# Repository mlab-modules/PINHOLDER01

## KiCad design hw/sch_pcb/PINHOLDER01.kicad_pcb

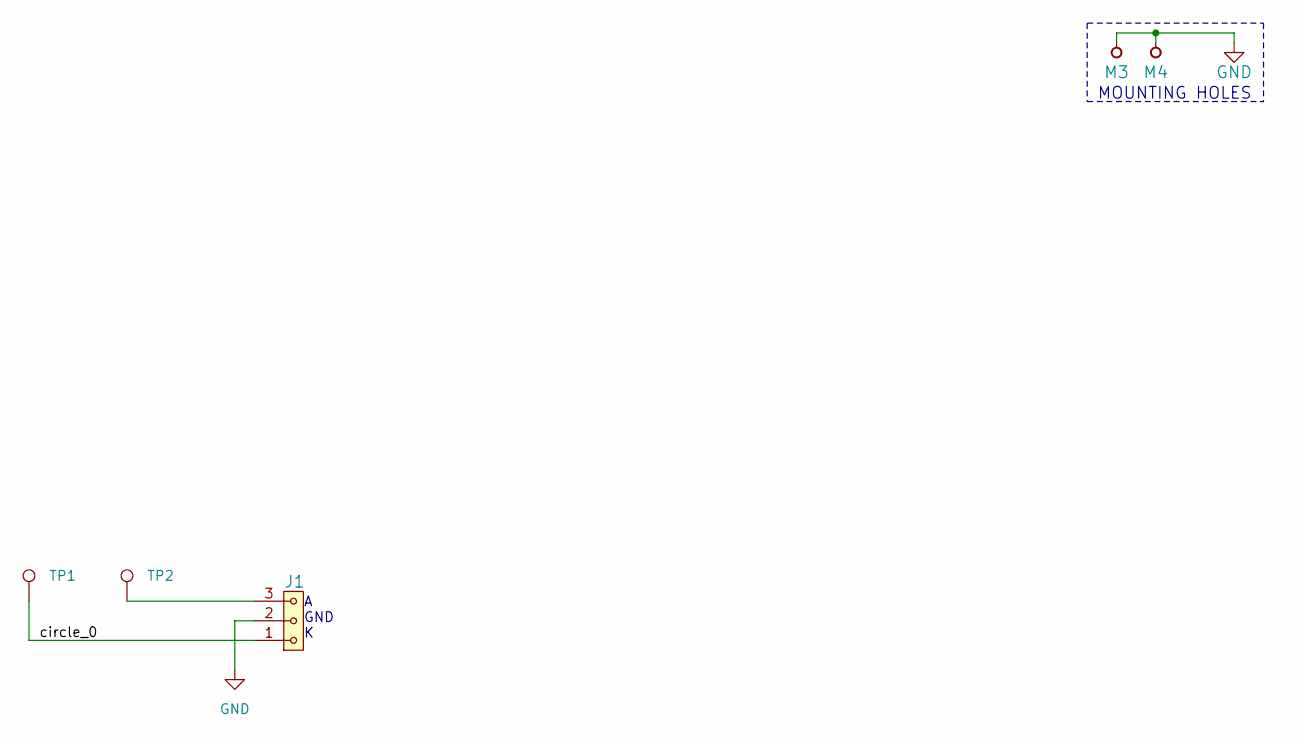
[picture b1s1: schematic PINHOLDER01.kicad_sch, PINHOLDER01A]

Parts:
J1: HEADER_1x03; PinHeader_1x03_P2.54mm_Vertical_SMD_Pin1Left
M3, M4: HOLE; MountingHole_3mm
TP1, TP2: TestPoint; TestPoint_Pad_D0.5mm_noSilk

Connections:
/circle_0: J1.1, TP1.1
GND: J1.2, M3.1, M4.1
unnamed: J1.3, TP2.1

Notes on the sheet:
MOUNTING HOLES
A GND K

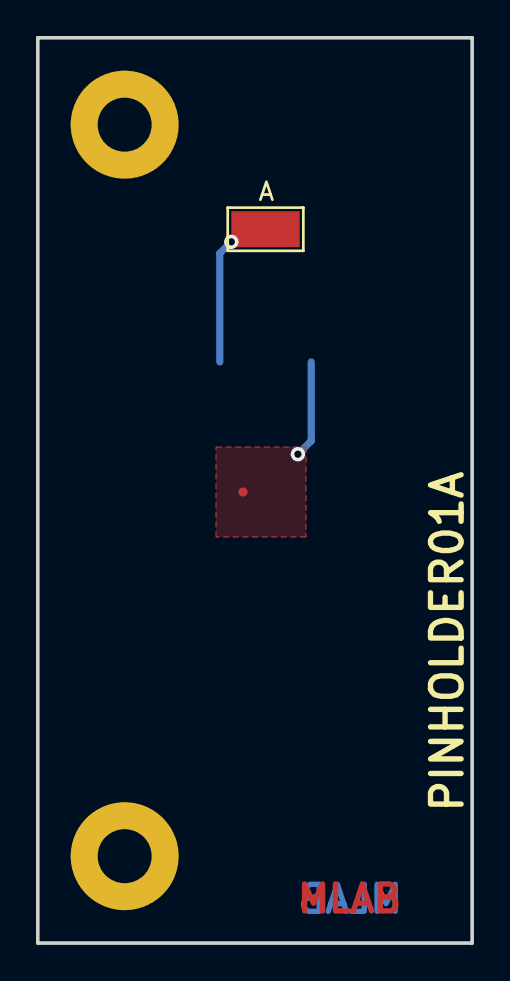
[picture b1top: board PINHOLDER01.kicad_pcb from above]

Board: 2 copper layers, 24.1 x 50.3 mm, 5 parts (1 on the bottom side), 3 nets.

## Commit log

2023-04-12 Copy name to bottom silkscreen. Fix path to title block template.
2023-04-12 Update metadata files
2023-04-13 Update workflow files
2023-04-13 Update actions products
2023-04-13 Edit PCB
2023-04-13 zamena anoda-katoda
2023-04-13 cleanup repository.
2023-04-13 Ortogonal shape Fit to USTSIPIN02A
2023-04-13 Add dimensions.
2023-04-13 update submodule
2023-05-25 automated commit; add github actions
2023-07-05 automated commit; rename source files to new naming convence
2023-09-16 Update image to image_title
2023-09-16 Update status
2025-02-22 Update metadata.yaml
    Decrease module mark.
